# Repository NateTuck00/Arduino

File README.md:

# Arduino
Work's arduino files

This is my collection of code I've written for work over the summer of 2021. 
Wiring schematics and datasheets for external parts can be provided.
Both of my main projects run a real time control system. Not all code in this library is written on interrupt driven code, but all code will be on a clock in final implementation.

Projects included:
  -Using an arduino Uno to control a linear actuator testing clutches with a pressure sensor, h bridge drive for the 12V motor, button input on an LCD shield, and exporting the data to an SD card
  
  -Using an arduino Leonardo with a PID and clamping techniques to monitor and control cabin air temp in an S10 with PWM control on a Chevy Cruze heating core.

UNO: This project runs on a 25 ms clock. The uno has an LCD, SD reader, and external protoshield for CAPs, resistors, and needed ICs. Depending on the actuator used, whether you use shutoff switches at the end, time in millis, or the bounds of the actuator... the actual implementation of actuator control can obviously vary based on the task, but this provides a good example if you do want to use real time control of a linear actuator. 

LEONARDO: This project runs on a 25 ms clock due mainly to i2c time with the LCD screen. Without the screen a 10 ms interrupt is easily achievable, but good temperature control is easily possible without it. Overclocking the screen or i2c protocol also allows 10 ms. Writing one's own library like the https://github.com/bitbank2/BitBang_I2C library is obviously possible as well for even more speed optimization if one was using a very strong heater core in a small space with need for fast control. 

ZERO: I used an arduino Zero with Pi-Hole to reroute my DNS in my house and block all ads across our entire wifi network

TIMERS
  The timers in this code can be different for people unexperienced with Arduino Registers and timers. Basically, Arduinos come with several timers (3 or more usually) and by  setting a count number and prescaler multiple to increment your counter by. The rest of the code is standard C with the use of documented libraries. By following the guide at https://www.instructables.com/Arduino-Timer-Interrupts/ you should be able to understand and copy what I've done here.

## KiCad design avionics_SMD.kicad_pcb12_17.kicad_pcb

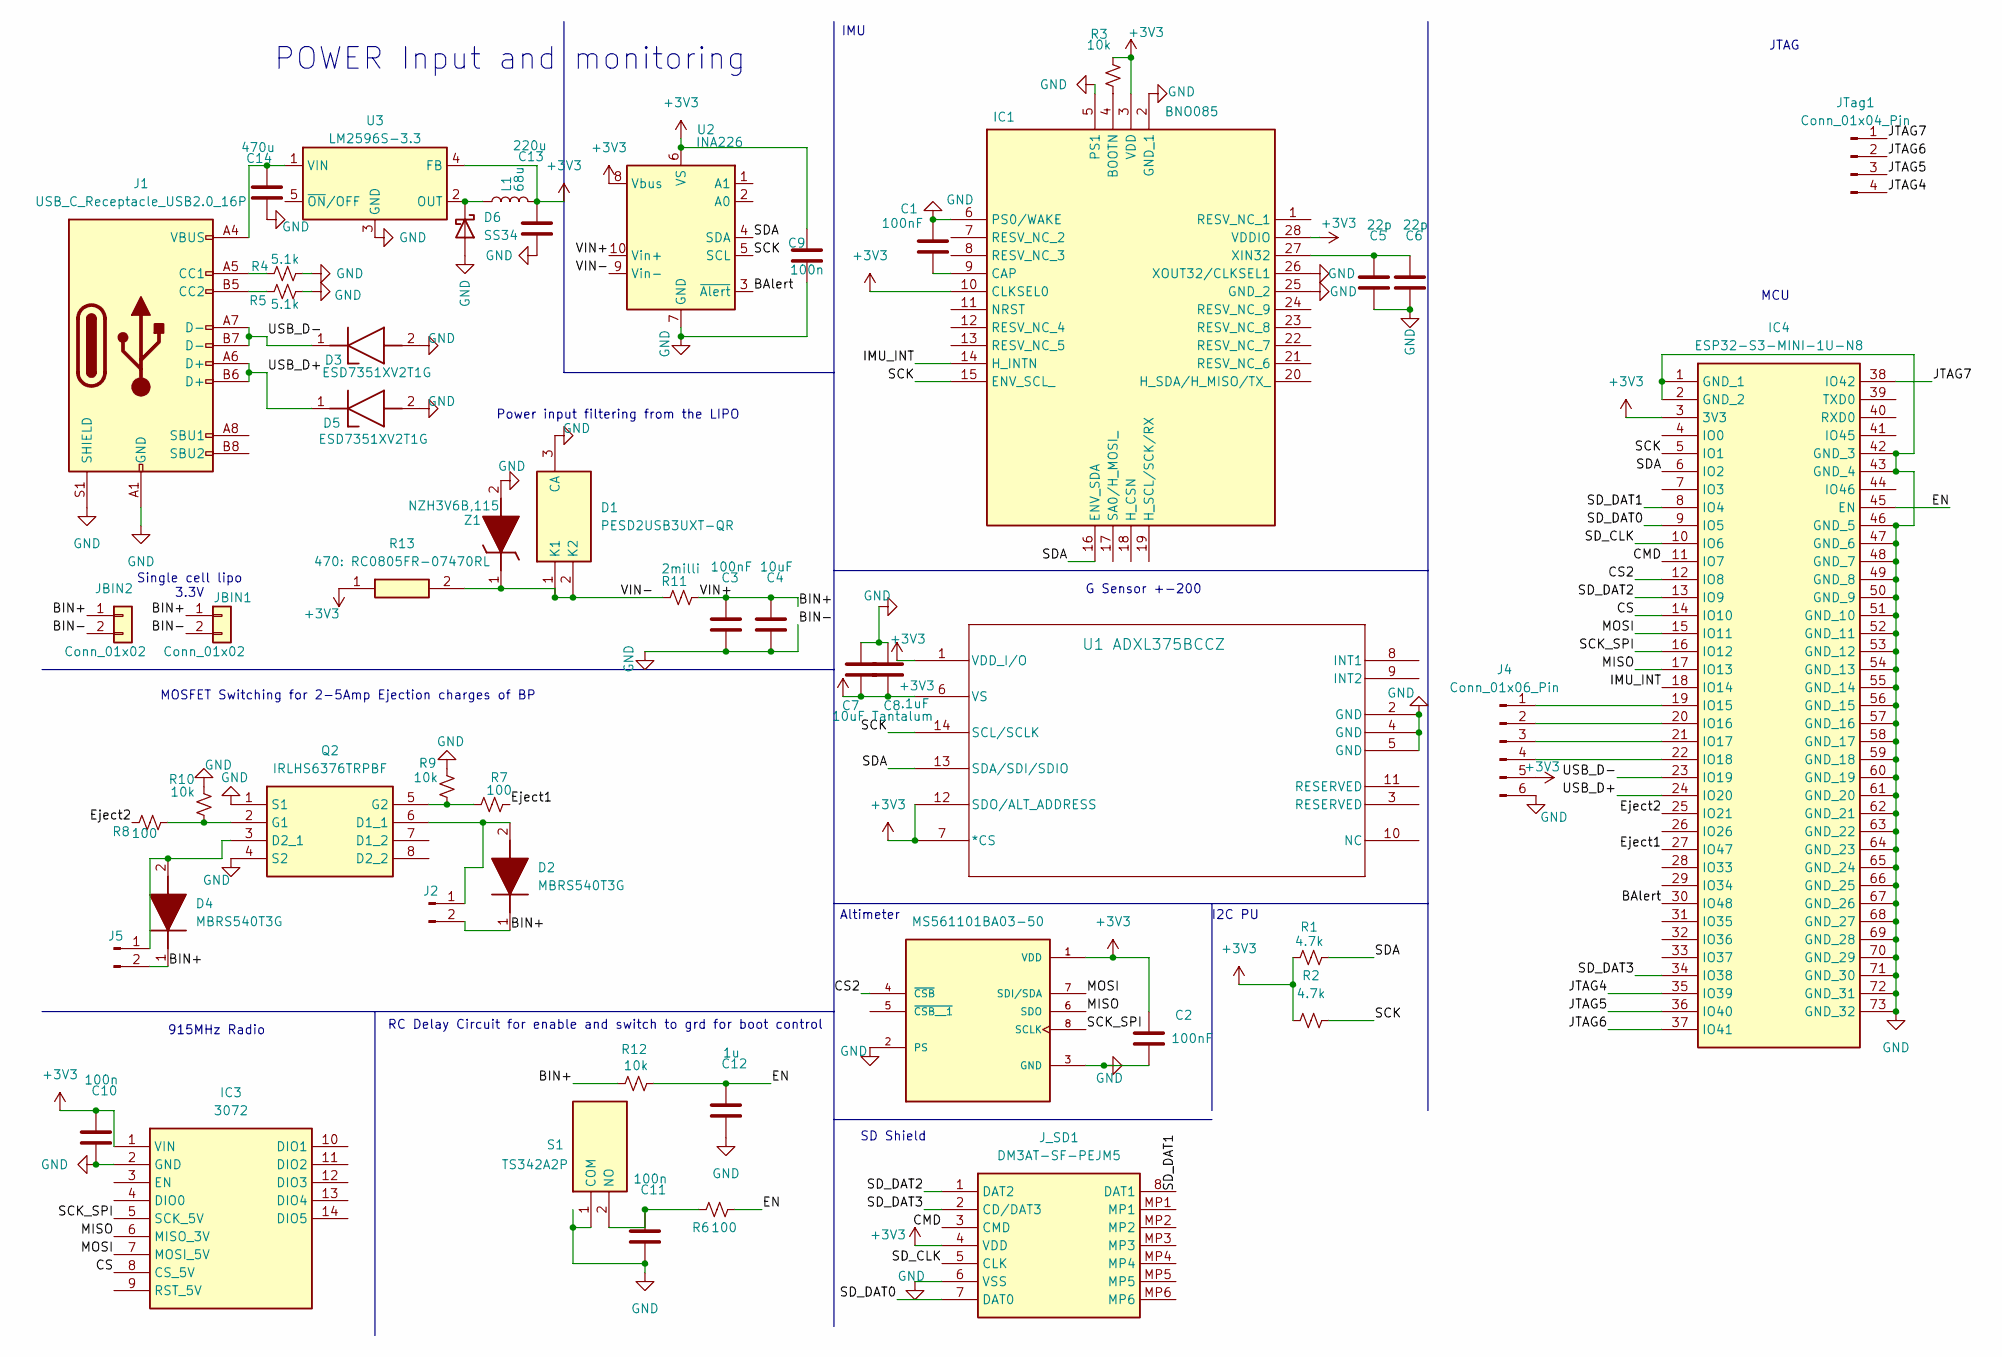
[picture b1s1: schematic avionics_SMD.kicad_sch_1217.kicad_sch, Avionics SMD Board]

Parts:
A1: MS561101BA03-50; XDCR_MS561101BA03-50; PARTREV 06/2017
C1, C2, C3: 100nF; C_0603_1608Metric
C4: 10uF; C_0805_2012Metric
C5, C6: 22p; C_0603_1608Metric
C7: 10uF Tantalum; C_0805_2012Metric
C8: .1uF; C_0603_1608Metric
C9, C10, C11: 100n; C_0603_1608Metric
C12: 1u; C_0603_1608Metric
C13: 220u; C_0603_1608Metric
C14: 470u; C_0603_1608Metric
D1: PESD2USB3UXT-QR; SOT95P230X110-3N; Manufacturer_Part_Number PESD2USB3UXT-QR; Mouser Part Number 771-PESD2USB3UXT-QR
D2, D4: MBRS540T3G; DIOM7958X256N; Manufacturer_Part_Number MBRS540T3G; Mouser Part Number 863-MBRS540T3G
D3, D5: ESD7351XV2T1G; SODFL1608X70N; Manufacturer_Part_Number ESD7351XV2T1G; Mouser Part Number 863-ESD7351XV2T1G
D6: SS34; D_SMA
IC1: BNO085; Manufacturer_Part_Number BNO085; Mouser Part Number 526-BNO085
IC3: 3072; Manufacturer_Part_Number 3072; Mouser Part Number 485-3072
IC4: ESP32-S3-MINI-1U-N8; ESP32S3MINI1UN8; Manufacturer_Part_Number ESP32-S3-MINI-1U-N8; Mouser Part Number 356-ESP32S3MINI1UN8
J1: USB_C_Receptacle_USB2.0_16P; USB_C_Receptacle_JAE_DX07S016JA1R1500
J2, J5: Conn_01x02_Pin; JST_PH_B2B-PH-K_1x02_P2.00mm_Vertical
J4: Conn_01x06_Pin; PinHeader_1x06_P2.54mm_Vertical
JBIN1, JBIN2: Conn_01x02; JST_PH_B2B-PH-K_1x02_P2.00mm_Vertical
JTag1: Conn_01x04_Pin; PinHeader_1x04_P2.54mm_Vertical
J_SD1: DM3AT-SF-PEJM5; DM3ATSFPEJM5; Manufacturer_Part_Number DM3AT-SF-PEJM5; Mouser Part Number 798-DM3AT-SF-PEJM5
L1: 68u; L_0603_1608Metric
Q2: IRLHS6376TRPBF; Manufacturer_Part_Number IRLHS6376TRPBF; Mouser Part Number 942-IRLHS6376TRPBF
R1, R2: 4.7k; R_0603_1608Metric
R3, R9, R10, R12: 10k; R_0603_1608Metric
R4, R5: 5.1k; R_0603_1608Metric
R6, R7, R8: 100; R_0603_1608Metric
R11: 2milli; R_0603_1608Metric
R13: 470: RC0805FR-07470RL; RESC2012X60N; Manufacturer_Part_Number RC0805FR-07470RL; Mouser Part Number 603-RC0805FR-07470RL
S1: TS342A2P; Manufacturer_Part_Number TS342A2P
U1: ADXL375BCCZ; LGA_CC-14-1_ADI-M
U2: INA226; VSSOP-10_3x3mm_P0.5mm
U3: LM2596S-3.3; TO-263-5_TabPin3
Z1: NZH3V6B,115; SODFL3516X120N; Manufacturer_Part_Number NZH3V6B,115; Mouser Part Number 771-NZH3V6B-115

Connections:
+3V3: A1.1 (VDD), C2.1, C7.2, C8.2, C9.1, C10.1, C13.1, IC1.3 (VDD), IC1.10 (CLKSEL0), IC1.28 (VDDIO), IC3.1 (VIN), IC4.3 (3V3), J4.5, J_SD1.4 (VDD), L1.2, R1.1, R2.1, R3.2, R13.1, U1.1 (VDD_I/O), U1.6 (VS), U1.7 (*CS), U1.12 (SDO/ALT_ADDRESS), U2.6 (VS), U2.8 (Vbus), U3.4 (FB)
/BAlert: IC4.30 (IO48), U2.3 (~Alert)
/BIN+: C3.1, C4.1, D2.1 (K), D4.1 (K), J2.2, J5.2, JBIN1.1, JBIN2.1, R11.1, R12.1, U2.10 (Vin+)
/CMD: IC4.11 (IO7), J_SD1.3 (CMD)
/CS: IC3.8 (CS_5V), IC4.14 (IO10)
/CS2: A1.4 (~CSB), IC4.12 (IO8)
/EN: C12.1, IC4.45 (EN), R6.2, R12.2
/Eject1: IC4.27 (IO47), R7.1
/Eject2: IC4.25 (IO21), R8.1
/IMU_INT: IC1.14 (H_INTN), IC4.18 (IO14)
/JTAG4: IC4.35 (IO39), JTag1.4
/JTAG5: IC4.36 (IO40), JTag1.3
/JTAG6: IC4.37 (IO41), JTag1.2
/JTAG7: IC4.38 (IO42), JTag1.1
/MISO: A1.6 (SDO), IC3.6 (MISO_3V), IC4.17 (IO13)
/MOSI: A1.7 (SDI/SDA), IC3.7 (MOSI_5V), IC4.15 (IO11)
/SCK: IC1.15 (ENV_SCL_), IC4.5 (IO1), R2.2, U1.14 (SCL/SCLK), U2.5 (SCL)
/SCK_SPI: A1.8 (SCLK), IC3.5 (SCK_5V), IC4.16 (IO12)
/SDA: IC1.16 (ENV_SDA), IC4.6 (IO2), R1.2, U1.13 (SDA/SDI/SDIO), U2.4 (SDA)
/SD_CLK: IC4.10 (IO6), J_SD1.5 (CLK)
/SD_DAT0: IC4.9 (IO5), J_SD1.7 (DAT0)
/SD_DAT1: IC4.8 (IO4), J_SD1.8 (DAT1)
/SD_DAT2: IC4.13 (IO9), J_SD1.1 (DAT2)
/SD_DAT3: IC4.34 (IO38), J_SD1.2 (CD/DAT3)
/USB_D+: D5.1 (K), IC4.24 (IO20), J1.A6 (D+), J1.B6 (D+)
/USB_D-: D3.1 (K), IC4.23 (IO19), J1.A7 (D-), J1.B7 (D-)
/VIN-: D1.1 (K1), D1.2 (K2), R11.2, R13.2, U2.9 (Vin-), Z1.1 (K)
GND: A1.2 (PS), A1.3 (GND), C1.2, C2.2, C3.2, C4.2, C5.2, C6.2, C7.1, C8.1, C9.2, C10.2, C11.2, C12.2, C13.2, C14.2, D1.3 (CA), D3.2 (A), D5.2 (A), D6.2 (A), IC1.2 (GND_1), IC1.5 (PS1), IC1.6 (PS0/WAKE), IC1.25 (GND_2), IC1.26 (XOUT32/CLKSEL1), IC3.2 (GND), IC4.1 (GND_1), IC4.2 (GND_2), IC4.42 (GND_3), IC4.43 (GND_4), IC4.46 (GND_5), IC4.47 (GND_6), IC4.48 (GND_7), IC4.49 (GND_8), IC4.50 (GND_9), IC4.51 (GND_10), IC4.52 (GND_11), IC4.53 (GND_12), IC4.54 (GND_13), IC4.55 (GND_14), IC4.56 (GND_15), IC4.57 (GND_16), IC4.58 (GND_17), IC4.59 (GND_18), IC4.60 (GND_19), IC4.61 (GND_20), IC4.62 (GND_21), IC4.63 (GND_22), IC4.64 (GND_23), IC4.65 (GND_24), IC4.66 (GND_25), IC4.67 (GND_26), IC4.68 (GND_27), IC4.69 (GND_28), IC4.70 (GND_29), IC4.71 (GND_30), IC4.72 (GND_31), IC4.73 (GND_32), J1.A1 (GND), J1.A12 (GND), J1.B1 (GND), J1.B12 (GND), J1.S1 (SHIELD), J4.6, JBIN1.2, JBIN2.2, J_SD1.6 (VSS), Q2.1 (S1), Q2.4 (S2), R4.2, R5.2, R9.2, R10.2, S1.1 (COM), U1.2 (GND), U1.4 (GND), U1.5 (GND), U2.7 (GND), U3.3 (GND), Z1.2 (A)
unnamed: D2.2 (A), J2.1, Q2.6 (D1_1)
unnamed: D4.2 (A), J5.1, Q2.3 (D2_1)
unnamed: D6.1 (K), L1.1, U3.2 (OUT)
unnamed: IC1.4 (BOOTN), R3.1
unnamed: C1.1, IC1.9 (CAP)
unnamed: C5.1, C6.1, IC1.27 (XIN32)
unnamed: IC4.19 (IO15), J4.1
unnamed: IC4.20 (IO16), J4.2
unnamed: IC4.21 (IO17), J4.3
unnamed: IC4.22 (IO18), J4.4
unnamed: J1.A5 (CC1), R4.1
unnamed: J1.B5 (CC2), R5.1
unnamed: Q2.2 (G1), R8.2, R10.1
unnamed: Q2.5 (G2), R7.2, R9.1
unnamed: C11.1, R6.1, S1.2 (NO)
unnamed: C14.1, J1.A4 (VBUS), J1.A9 (VBUS), J1.B4 (VBUS), J1.B9 (VBUS), U3.1 (VIN)

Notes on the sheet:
915MHz Radio
SD Shield
Single cell lipo 3.3V
MOSFET Switching for 2-5Amp Ejection charges of BP
MCU
IMU
Altimeter
RC Delay Circuit for enable and switch to grd for boot control
G Sensor +-200
POWER Input and monitoring
JTAG
I2C PU
Power input filtering from the LIPO

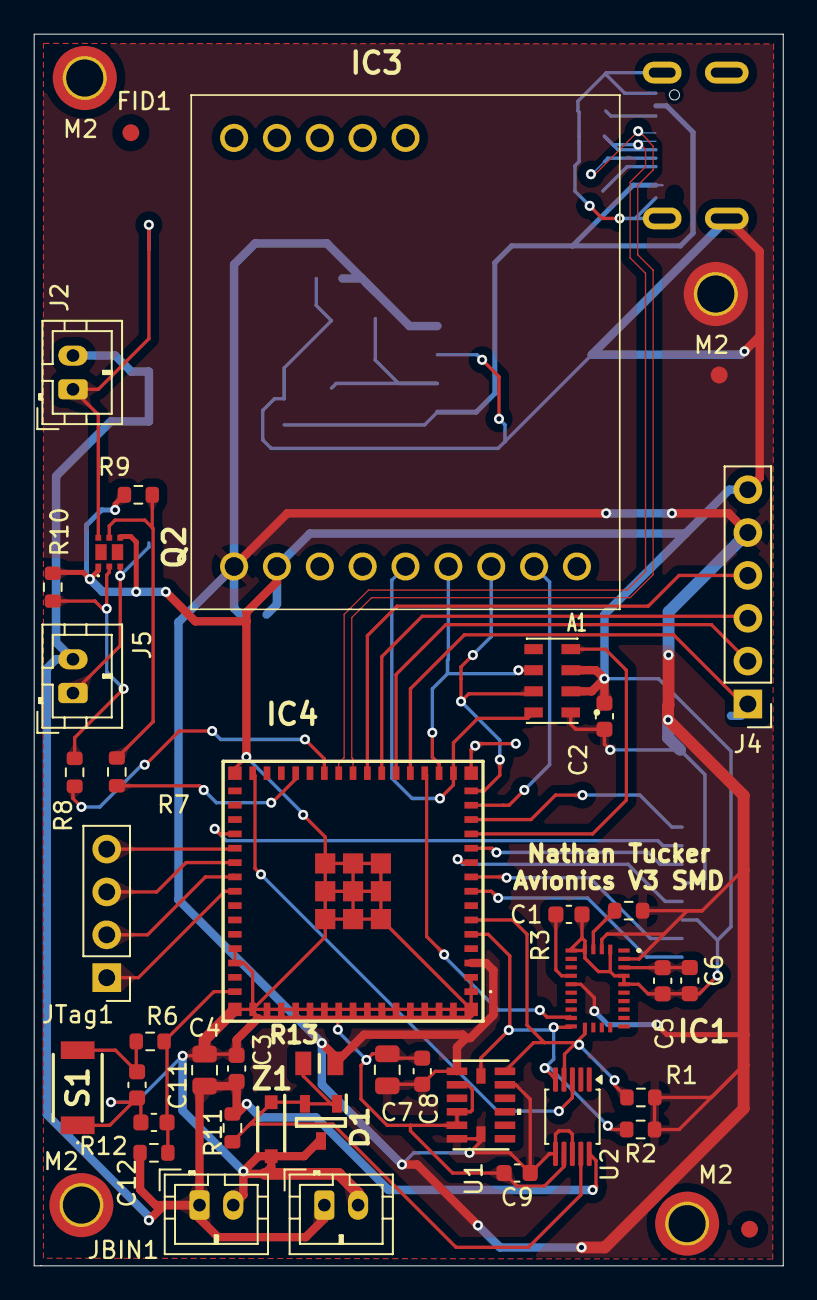
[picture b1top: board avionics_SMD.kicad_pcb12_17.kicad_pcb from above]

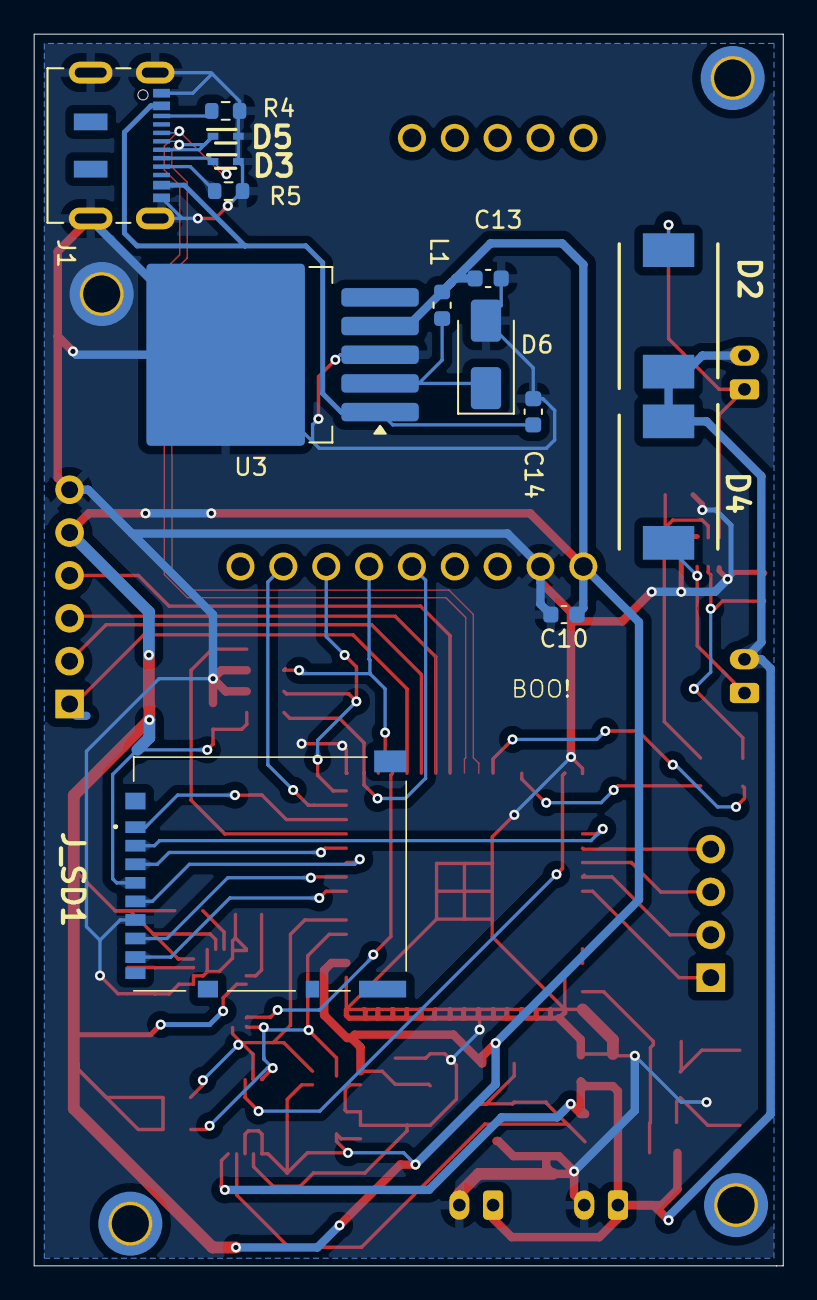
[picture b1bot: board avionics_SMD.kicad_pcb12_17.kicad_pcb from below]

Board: 2 copper layers, 44.4 x 73.0 mm, 57 parts (14 on the bottom side), 44 nets.

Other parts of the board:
FID1: Fiducial_1mm_Mask2mm
M2, M2#2, M2#3, M2#4: MountingHole_2.2mm_M2_DIN965_Pad_TopBottom

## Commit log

2021-06-30 First_commit
2021-06-30 Tested
2021-07-01 end of day. Button control
2021-07-01 Fixed clock to 25 ms and adjusted consecutive button presses
2021-07-01 Create README.md
    ReadMe 7/1
2021-07-01 Update README.md
    grammar
2021-07-01 manual control and disaster started in handle_buttons()
2021-07-01 ISR control manual motor
2021-07-06 comments
2021-07-06 Fixed pause inconsistency. Note This compiles with high memory usage warning, but runs consistently.
2021-07-06 cleaned up variables before bitwise memory change
2021-07-07 Bitwise operations done to save memory.
2021-07-07 Example of bitwise operations done in UNO interrupt_actuator project
2021-07-07 SD on arduino. Used in actuator
2021-07-07 spacing
2021-07-08 60,000 clock. Initial running program for leonardo Not State-Machined out in loop like how I'd like it to be
2021-07-08 Redid state machine. Display having issues when added. Take out serial and figure out display
2021-07-08 display having issues in time. Library swap in order
2021-07-09 Fastest SSD1306 library (19-23 ms)
2021-07-09 New display library incorporated entirely. This Entire project runs on a 25 ms clock. Ready to test in car to see how PID behaves. Clock can be adjusted to an even faster 2 stage design by combining 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
2021-07-09 Shows how concat can be used (and was used in the main project!) The timing of this project led to the choice to use it as the overall new display library
2021-07-09 2 stage speedy version of the code with the 3rd stage commented out. This isn't guaranteed to be stable. 3ms of overhead and those 3ms are used to do string concats...
2021-07-09 Fixed 32.00 startup. Now if the sensor isn't connected or there's a weak connection, the display says "starting up"
2021-07-12 First commit to be tested before deploying on leonardo and temp project
2021-07-12 Old backup display speedtest
2021-07-12 Adafruit display speed test w oscope on pin 6. Can also use millis(). This library was too slow for me. display.display() alone took ~19 ms and then writing to the memory buffer took 6 ideally. My ne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
2021-07-12 Watchdog incorporated. 8 second timeout after sensor readings. Says "Reading Temp.." and waits for sensor to be reconnected
2021-07-12 reset on timeout
2021-07-12 handled timeout of sensor
2021-07-12 Medium numbers don't have spaces or letters defined. We'll need a display timeout from changing set temp to just showing current.
2021-07-13 temp display shows set temp for one cycle
2021-07-13 Display times out on changing set temp. PWM works with 12v pull-up. Project works entirely. Time to build a box around it
2021-07-13 Used to print floats with a space (predetermined offset)
2021-07-14 Tuned PID and reversed it to actually heat when you set the temperature high instead of shutting the heat off and doing the temp control backwards
2021-07-15 Cleaned and removed Serial
2021-07-15 Separated working temp code into tabs and header files.
2021-07-15 tagged variable names and decluttered code for future use
2021-07-15 added the checkTempBounds file and organized more code
2021-07-16 Entirely new temperature sensor library (dht). Added in as a header and cpp for reusable code. This new library never misses pings.
2021-07-16 The dht library doesn't use interrupts like the sparkfun RHT03 library does, but the dht22 is the same as the RHT03. This library works much better for my use case, and never tosses checksum errors
2021-07-19 Swapped serial and tested with error codes
2021-07-19 Added battery voltage checker and error code flashing with it and failing to reach targeted temp in time
2021-07-19 Serial speed
2021-07-21 Fixed reset for display on initial plug into power
2021-07-21 Quick mock up if you're worried you've shorted 5V to your analog pins and want to one by one check if they work
2021-07-21 Tuned PID for sharper cutoff, added output print to screen to check heater function. At this point, the Arduino has successfully ran in the car and has ran the heater
2021-07-22 added display Logic tab and did a cleanse of comments and spacing
2021-07-22 cleaned and ready version of code to be reviewed. Working in car. Waiting on hardware
2021-07-29 Fixed battery voltage reading. Waiting on final display case to put in car.
2021-07-29 9600
2021-08-02 Final Commit. Arduino is sealed in car
2021-08-03 How I'll control the actuator on a interrupt
2021-08-03 Relay control changes but not permanent
2021-08-03 Hbridge duty cycle control without smart logic
2021-08-03 new funcs
2021-08-03 pressureSensor testing
2021-08-05 Saved Some Ram in serial
2021-08-05 Massive Ram savings. Program crashes on runTest as expected, but once new and gate comes in and I follow HBridgeTest, the actuator control should work.
2021-08-06 added #ifdefs in for serial and for display logic to show the output value of the heater /255
2021-08-06 Added #ifdefs for serial out
2021-08-09 Setup Debug
2021-08-09 To write my actuators low in case of hardware issue
2021-08-09 Fixed the pause screen back to working and displaying a two second screen for now. We know what to do once I get parts in
2021-08-12 watchdog added, pin 1 swapped to 3, running on benchtop. Lots of changes. Almost done
2021-08-16 statics and comments
2021-08-17 THIS SHOULD NOT WORK BUT DOES.
    -Swapped the switches to read low instead of high. I think that the millis timer got interrupted before and was unable to count the time because I also had to take out the timeout in the software to 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
    - How this can be fixed: My code needs to have a retract and extend function in 3 and 4 that set a flag and a new 5 ms ISR that checks if those flags are set {read microswitch and shutoff if hit}
    -The SD card logging is not written in
    -The overcurrent protection needs its own stage or to go in one that isn't very full.
    -The 25 ms clock that won't be on an ISR anymore could measure pressure on every 4th iteration to get 100 ms average pressu
2021-08-19 swapped pins
2021-08-19 This code extends one time, measures the PSI the max amount of times I could fit into ram for one extension, and then retracts and shows all of the numbered pressure readings on screen
2021-08-19 Fixed how PSI is measured, added new ISR variables needed to count out 3 and 10 seconds for extension/retraction timeout and duty cycle wait respectively.
    The 7 states should give plenty of free time.
    Needs Fixed/finished:
    -This code no longer calls the runtest function that worked but violated interrupts and RTC rules
    -There is no overcurrent protection (analog read A3)
    -myFile.available() needs called somewhere to make sure we don't overload the SD card one weekend and lose the critical PSI measurements that caught a failure.
    -3 second and 10 second timeouts need written in 25 ms ISR
2021-08-20 This code version fixed some issues, but it has a bad fix for an odd observed issue.
    The previous issue: Code unresponsive to holding down the right button (although button handler is visibly called and it was hitting my unpause case and setting the tests needed flag to being true.
    The half fix: Adding in if not reading on extension microswitch extending flag = true.
    This has some issues though because it doesn't activate the three second timer and
    once you actually hit the micro it doesn't retract or go into any other state, but it reads the pressure along the way
    I think I can fix this by setting the iterator for the ~25 ms "ISR" to be on the pretest logic state (or 1 before depending on
2021-08-20 Pressure and Current sense optimized
2021-08-20 5 ms clock code used in the organized actuator
2021-08-20 This version measures and logs the tests, current, and pressure.
    I need to swap the way the pressure is logged so that it's logged into the dataString within its own function to improve consistency if the processor gets overloaded.
    The words in the datalogs are not needed
2021-08-20 Made the datalogging output CSV friendly. Need to test on bench and potentially add check in isr that if both retracting and extending read true to read the data pins and if in the middle retract unt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
    Measure current doesn't have the math in it to stop for a current yet or convert the analog read value to a voltage.
    No manual motor control is written in although handle_buttons describes how we would do this and set the disaster flag if we hit that overcurrent
2023-01-05 Gardening Device first pass
    This code uses a photoresistor and thermistor I have spare to measure temperature and lumens and display them on an OLED with a plant health status at the bottom. In the future, soil moisture will be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
2025-12-17 Added PCB Schematic for Avionics
    ESP32-S3-Mini-1U controlling an IMU, Accelerometer, altimeter, and black powder ejection charge (Rocket)
    BNO085,MS5611,ADXL375 sensors. Lora GPS and radio communications on 915MHz
